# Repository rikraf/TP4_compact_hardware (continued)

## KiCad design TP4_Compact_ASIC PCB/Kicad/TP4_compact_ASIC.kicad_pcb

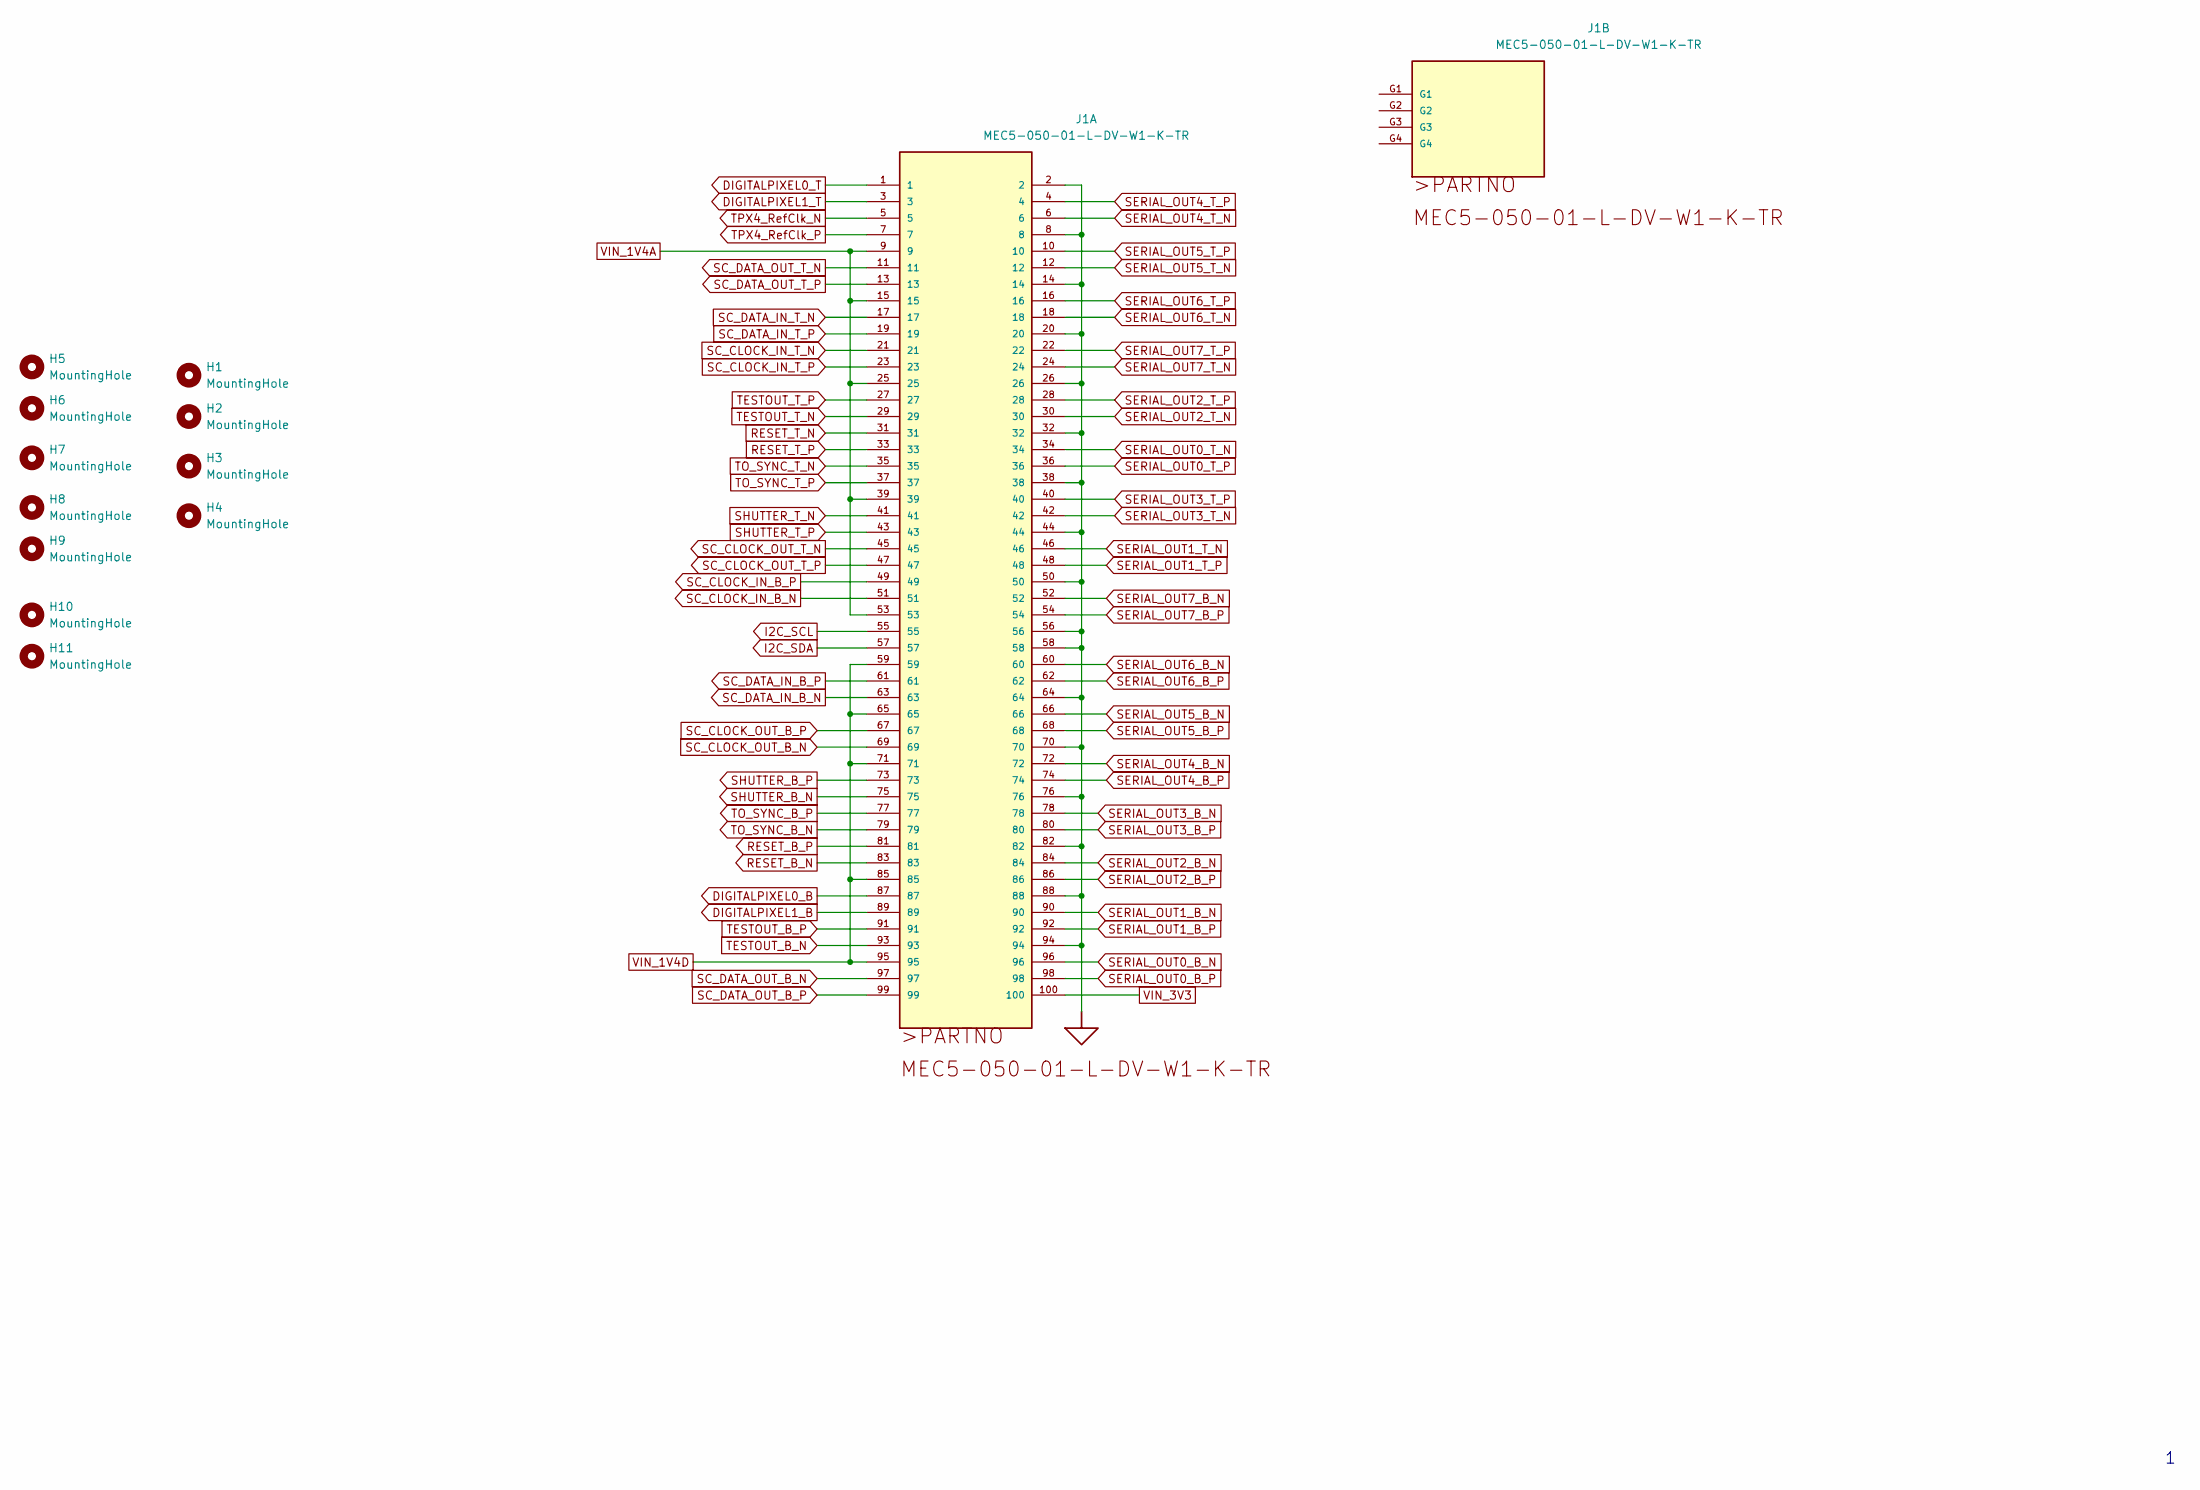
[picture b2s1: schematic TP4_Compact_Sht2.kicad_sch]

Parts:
H1, H2, H3, H4: MountingHole; hole_2.4mm
H5, H6, H7, H8, H9: MountingHole; pad_5.3_3.0mm
H10, H11: MountingHole; hole_1.7mm
J1: MEC5-050-01-L-DV-W1-K-TR; MANUFACTURER PART NUMBER MEC5-050-01-L-DV-W1-K-TR

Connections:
DIGITALPIXEL0_B: J1.87; also elsewhere on the board
DIGITALPIXEL0_T: J1.1; also elsewhere on the board
DIGITALPIXEL1_B: J1.89; also elsewhere on the board
DIGITALPIXEL1_T: J1.3; also elsewhere on the board
GND: J1.2, J1.8, J1.14, J1.20, J1.26, J1.32, J1.38, J1.44, J1.50, J1.56, J1.58, J1.64, J1.70, J1.76, J1.82, J1.88, J1.94; also elsewhere on the board
I2C_SCL: J1.55; also elsewhere on the board
I2C_SDA: J1.57; also elsewhere on the board
RESET_B_N: J1.83; also elsewhere on the board
RESET_B_P: J1.81; also elsewhere on the board
RESET_T_N: J1.31; also elsewhere on the board
RESET_T_P: J1.33; also elsewhere on the board
SC_CLOCK_IN_B_N: J1.51; also elsewhere on the board
SC_CLOCK_IN_B_P: J1.49; also elsewhere on the board
SC_CLOCK_IN_T_N: J1.21; also elsewhere on the board
SC_CLOCK_IN_T_P: J1.23; also elsewhere on the board
SC_CLOCK_OUT_B_N: J1.69; also elsewhere on the board
SC_CLOCK_OUT_B_P: J1.67; also elsewhere on the board
SC_CLOCK_OUT_T_N: J1.45; also elsewhere on the board
SC_CLOCK_OUT_T_P: J1.47; also elsewhere on the board
SC_DATA_IN_B_N: J1.63; also elsewhere on the board
SC_DATA_IN_B_P: J1.61; also elsewhere on the board
SC_DATA_IN_T_N: J1.17; also elsewhere on the board
SC_DATA_IN_T_P: J1.19; also elsewhere on the board
SC_DATA_OUT_B_N: J1.97; also elsewhere on the board
SC_DATA_OUT_B_P: J1.99; also elsewhere on the board
SC_DATA_OUT_T_N: J1.11; also elsewhere on the board
SC_DATA_OUT_T_P: J1.13; also elsewhere on the board
SERIAL_OUT0_B_N: J1.96; also elsewhere on the board
SERIAL_OUT0_B_P: J1.98; also elsewhere on the board
SERIAL_OUT0_T_N: J1.34; also elsewhere on the board
SERIAL_OUT0_T_P: J1.36; also elsewhere on the board
SERIAL_OUT1_B_N: J1.90; also elsewhere on the board
SERIAL_OUT1_B_P: J1.92; also elsewhere on the board
SERIAL_OUT1_T_N: J1.46; also elsewhere on the board
SERIAL_OUT1_T_P: J1.48; also elsewhere on the board
SERIAL_OUT2_B_N: J1.84; also elsewhere on the board
SERIAL_OUT2_B_P: J1.86; also elsewhere on the board
SERIAL_OUT2_T_N: J1.30; also elsewhere on the board
SERIAL_OUT2_T_P: J1.28; also elsewhere on the board
SERIAL_OUT3_B_N: J1.78; also elsewhere on the board
SERIAL_OUT3_B_P: J1.80; also elsewhere on the board
SERIAL_OUT3_T_N: J1.42; also elsewhere on the board
SERIAL_OUT3_T_P: J1.40; also elsewhere on the board
SERIAL_OUT4_B_N: J1.72; also elsewhere on the board
SERIAL_OUT4_B_P: J1.74; also elsewhere on the board
SERIAL_OUT4_T_N: J1.6; also elsewhere on the board
SERIAL_OUT4_T_P: J1.4; also elsewhere on the board
SERIAL_OUT5_B_N: J1.66; also elsewhere on the board
SERIAL_OUT5_B_P: J1.68; also elsewhere on the board
SERIAL_OUT5_T_N: J1.12; also elsewhere on the board
SERIAL_OUT5_T_P: J1.10; also elsewhere on the board
SERIAL_OUT6_B_N: J1.60; also elsewhere on the board
SERIAL_OUT6_B_P: J1.62; also elsewhere on the board
SERIAL_OUT6_T_N: J1.18; also elsewhere on the board
SERIAL_OUT6_T_P: J1.16; also elsewhere on the board
SERIAL_OUT7_B_N: J1.52; also elsewhere on the board
SERIAL_OUT7_B_P: J1.54; also elsewhere on the board
SERIAL_OUT7_T_N: J1.24; also elsewhere on the board
SERIAL_OUT7_T_P: J1.22; also elsewhere on the board
SHUTTER_B_N: J1.75; also elsewhere on the board
SHUTTER_B_P: J1.73; also elsewhere on the board
SHUTTER_T_N: J1.41; also elsewhere on the board
SHUTTER_T_P: J1.43; also elsewhere on the board
TESTOUT_B_N: J1.93; also elsewhere on the board
TESTOUT_B_P: J1.91; also elsewhere on the board
TESTOUT_T_N: J1.29; also elsewhere on the board
TESTOUT_T_P: J1.27; also elsewhere on the board
TO_SYNC_B_N: J1.79; also elsewhere on the board
TO_SYNC_B_P: J1.77; also elsewhere on the board
TO_SYNC_T_N: J1.35; also elsewhere on the board
TO_SYNC_T_P: J1.37; also elsewhere on the board
TPX4_RefClk_N: J1.5; also elsewhere on the board
TPX4_RefClk_P: J1.7; also elsewhere on the board
VIN_1V4A: J1.9, J1.15, J1.25, J1.39, J1.53; also elsewhere on the board
VIN_1V4D: J1.59, J1.65, J1.71, J1.85, J1.95; also elsewhere on the board
VIN_3V3: J1.100; also elsewhere on the board

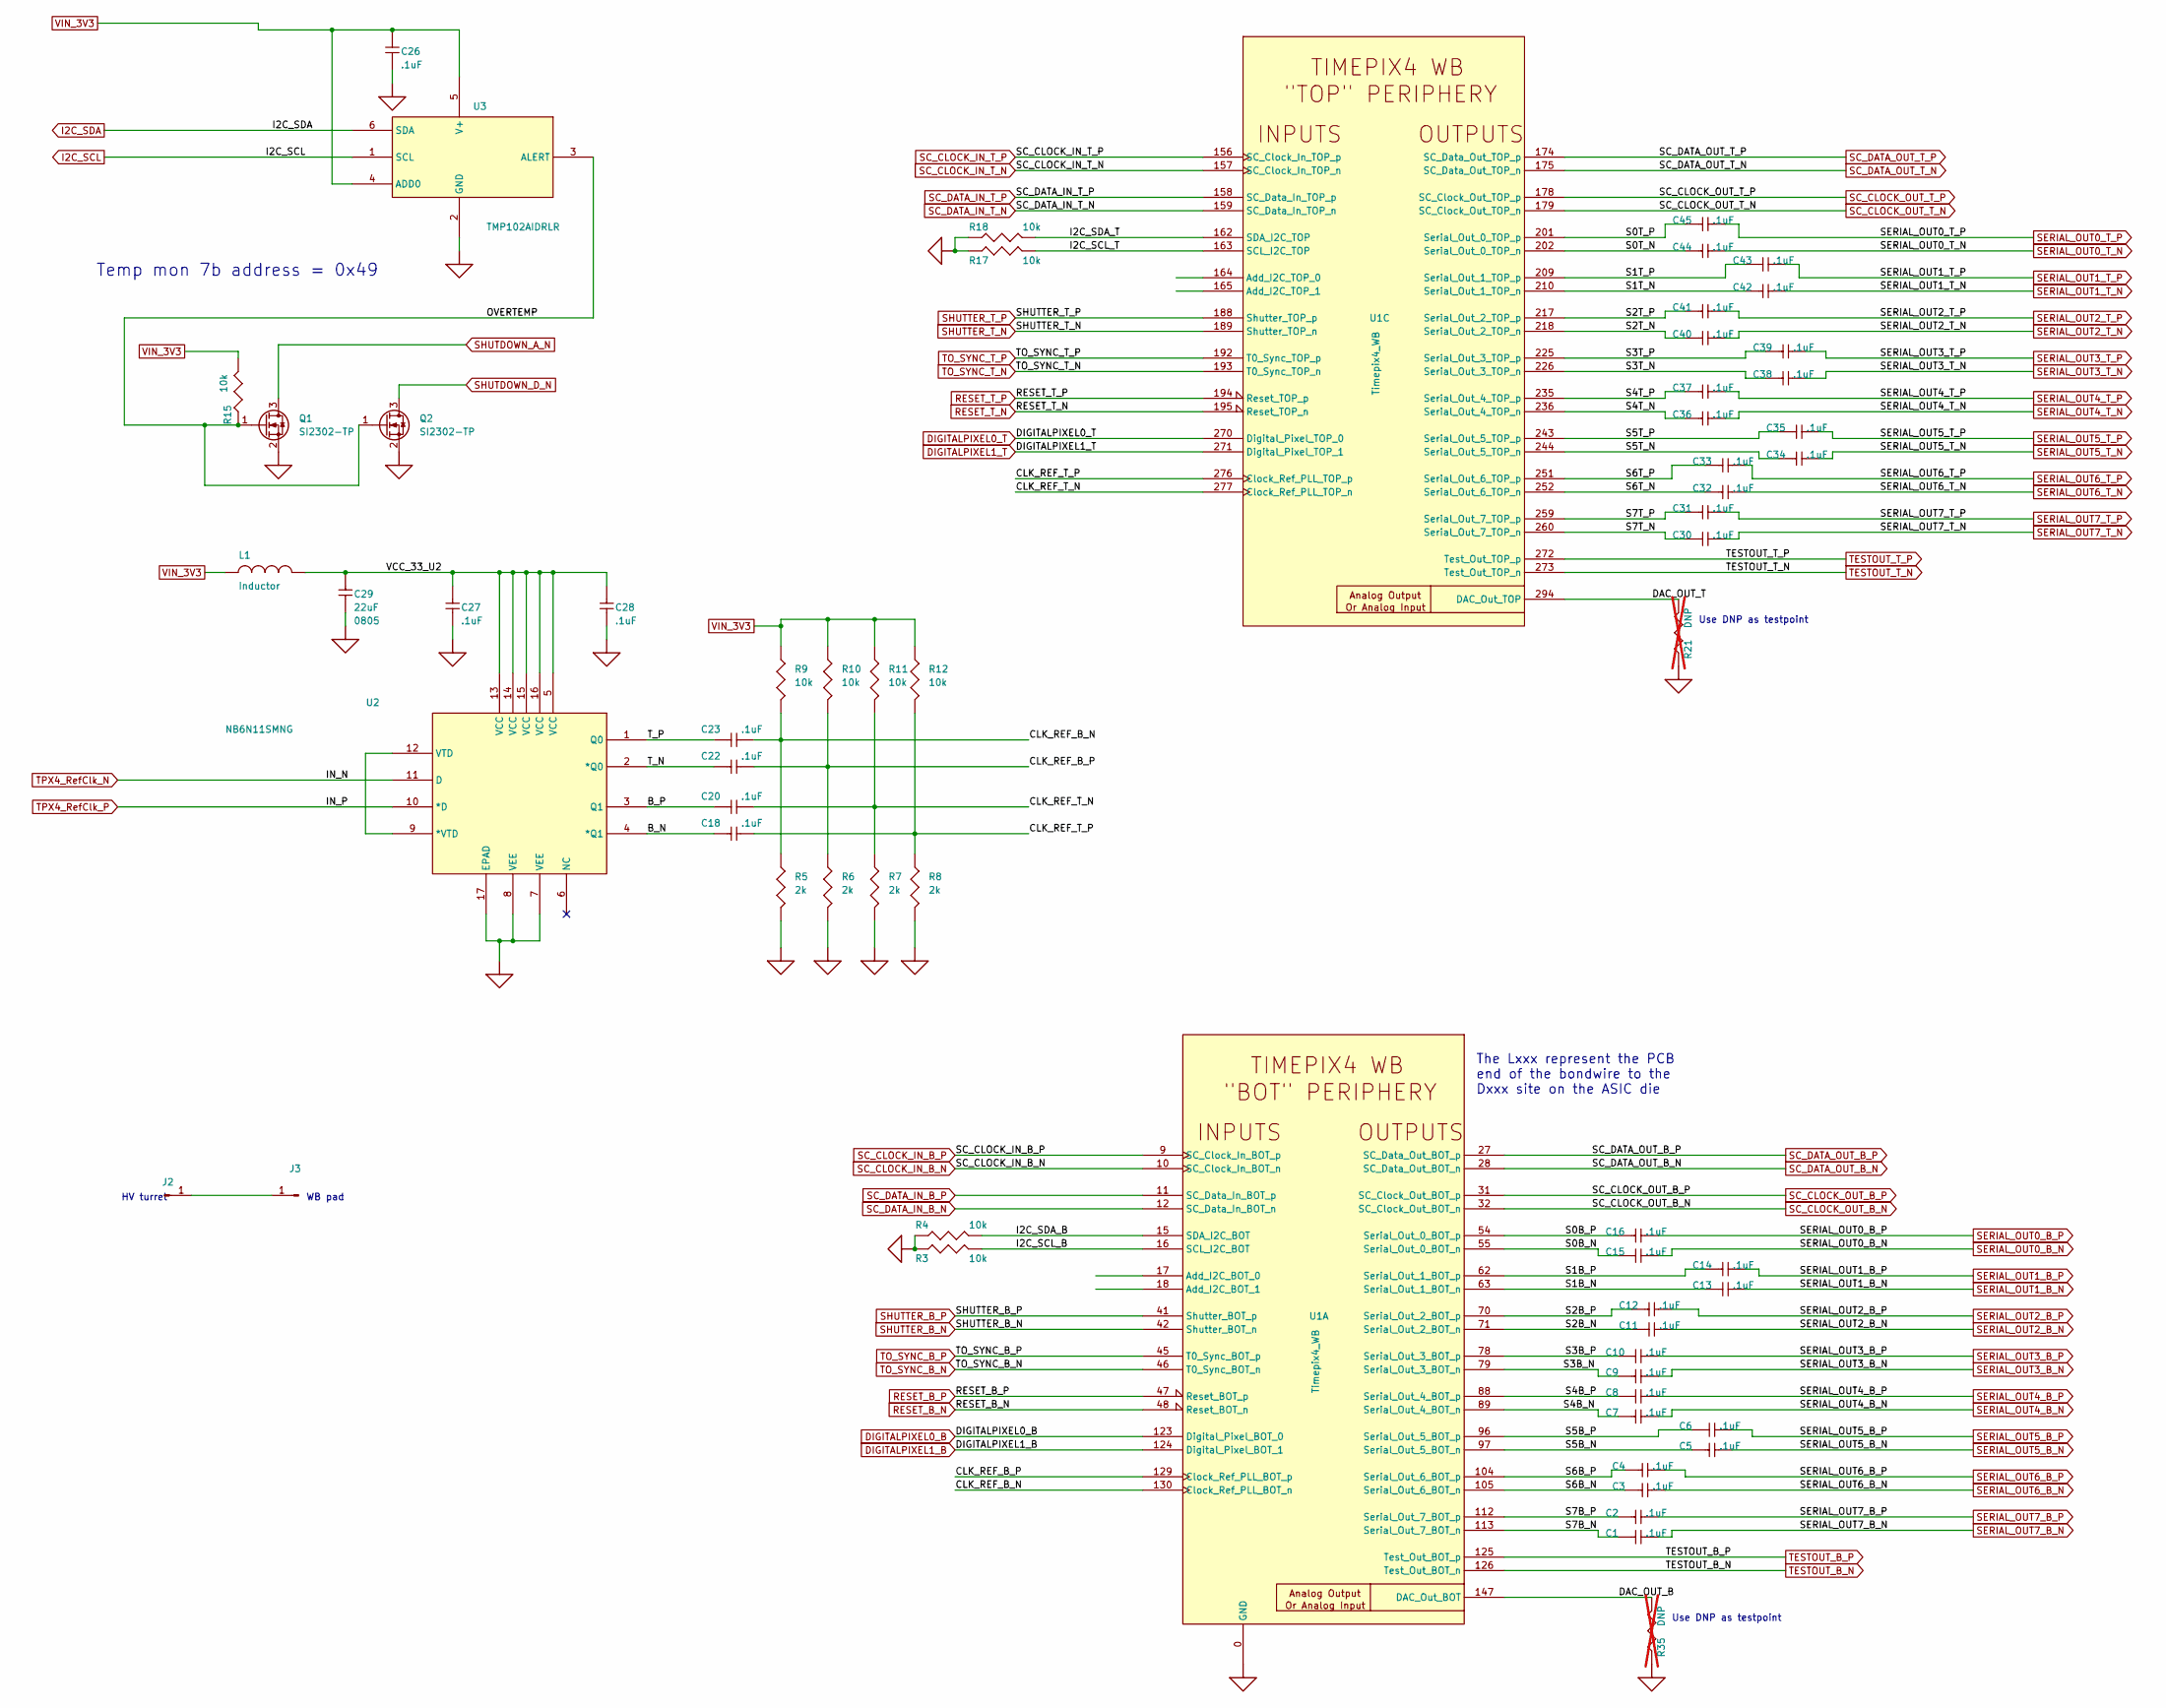
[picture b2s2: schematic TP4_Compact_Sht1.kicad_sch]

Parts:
C1, C2, C3, C4, C5, C6, C7, C8, C9, C10, C11, C12, C13, C14, C15, C16, C18, C20, C22, C23, C26, C27, C28, C30, C31, C32, C33, C34, C35, C36, C37, C38, C39, C40, C41, C42, C43, C44, C45: .1uF; C_0201_0603Metric; VOLTAGE - RATED 6.3V; TOLERANCE ±10%; MANUFACTURER PART NUMBER GRM033R61A104ME15D
C29: 22uF; C0805; VOLTAGE - RATED 10V; TOLERANCE ±10%; MANUFACTURER PART NUMBER CL21X226MQQNNNG
J2: Conn_01x01_Pin; PinHeader_1x01_P2.54mm_Vertical
J3: Conn_01x01_Pin; Single_WB_pad
L1: Inductor; L_0805_2012Metric; CURRENT RATING 4 Amps; MANUFACTURER PART NUMBER BLM21SP181BH1D
Q1, Q2: SI2302-TP; SOT-23; MANUFACTURER PART NUMBER SI2302-TP
R3, R4, R9, R10, R11, R12, R15, R17, R18: 10k; R_0402_1005Metric; MANUFACTURER PART NUMBER CR0402-FX-1002GLF
R5, R6, R7, R8: 2k; R_0402_1005Metric; MANUFACTURER PART NUMBER CR0402-FX-2001GLF
R21, R35: DNP; R_0402_1005Metric; not fitted
U1: Timepix4_WB; Timepix4_WB_nocaps
U2: NB6N11SMNG; QFN16_3x3_mm; MANUFACTURER_PART_NUMBER NB6L11SMNG
U3: TMP102AIDRLR; DRL6; MANUFACTURER_PART_NUMBER TMP102AIDRLR

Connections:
/ASIC_signals/B_N: C18.1, U2.4 (*Q1)
/ASIC_signals/B_P: C20.1, U2.3 (Q1)
/ASIC_signals/CLK_REF_B_N: C23.2, R5.2, R9.1, U1.130 (Clock_Ref_PLL_BOT_n)
/ASIC_signals/CLK_REF_B_P: C22.2, R6.2, R10.1, U1.129 (Clock_Ref_PLL_BOT_p)
/ASIC_signals/CLK_REF_T_N: C20.2, R7.2, R11.1, U1.277 (Clock_Ref_PLL_TOP_n)
/ASIC_signals/CLK_REF_T_P: C18.2, R8.2, R12.1, U1.276 (Clock_Ref_PLL_TOP_p)
/ASIC_signals/DAC_OUT_B: R35.2, U1.147 (DAC_Out_BOT)
/ASIC_signals/DAC_OUT_T: R21.2, U1.294 (DAC_Out_TOP)
/ASIC_signals/I2C_SCL_B: R3.2, U1.16 (SCL_I2C_BOT)
/ASIC_signals/I2C_SCL_T: R17.2, U1.163 (SCL_I2C_TOP)
/ASIC_signals/I2C_SDA_B: R4.2, U1.15 (SDA_I2C_BOT)
/ASIC_signals/I2C_SDA_T: R18.2, U1.162 (SDA_I2C_TOP)
/ASIC_signals/OVERTEMP: Q1.1 (G), Q2.1 (G), R15.1, U3.3 (ALERT)
/ASIC_signals/S0B_N: C15.1, U1.55 (Serial_Out_0_BOT_n)
/ASIC_signals/S0B_P: C16.1, U1.54 (Serial_Out_0_BOT_p)
/ASIC_signals/S0T_N: C44.1, U1.202 (Serial_Out_0_TOP_n)
/ASIC_signals/S0T_P: C45.1, U1.201 (Serial_Out_0_TOP_p)
/ASIC_signals/S1B_N: C13.1, U1.63 (Serial_Out_1_BOT_n)
/ASIC_signals/S1B_P: C14.1, U1.62 (Serial_Out_1_BOT_p)
/ASIC_signals/S1T_N: C42.1, U1.210 (Serial_Out_1_TOP_n)
/ASIC_signals/S1T_P: C43.1, U1.209 (Serial_Out_1_TOP_p)
/ASIC_signals/S2B_N: C11.1, U1.71 (Serial_Out_2_BOT_n)
/ASIC_signals/S2B_P: C12.1, U1.70 (Serial_Out_2_BOT_p)
/ASIC_signals/S2T_N: C40.1, U1.218 (Serial_Out_2_TOP_n)
/ASIC_signals/S2T_P: C41.1, U1.217 (Serial_Out_2_TOP_p)
/ASIC_signals/S3B_N: C9.1, U1.79 (Serial_Out_3_BOT_n)
/ASIC_signals/S3B_P: C10.1, U1.78 (Serial_Out_3_BOT_p)
/ASIC_signals/S3T_N: C38.1, U1.226 (Serial_Out_3_TOP_n)
/ASIC_signals/S3T_P: C39.1, U1.225 (Serial_Out_3_TOP_p)
/ASIC_signals/S4B_N: C7.1, U1.89 (Serial_Out_4_BOT_n)
/ASIC_signals/S4B_P: C8.1, U1.88 (Serial_Out_4_BOT_p)
/ASIC_signals/S4T_N: C36.1, U1.236 (Serial_Out_4_TOP_n)
/ASIC_signals/S4T_P: C37.1, U1.235 (Serial_Out_4_TOP_p)
/ASIC_signals/S5B_N: C5.1, U1.97 (Serial_Out_5_BOT_n)
/ASIC_signals/S5B_P: C6.1, U1.96 (Serial_Out_5_BOT_p)
/ASIC_signals/S5T_N: C34.1, U1.244 (Serial_Out_5_TOP_n)
/ASIC_signals/S5T_P: C35.1, U1.243 (Serial_Out_5_TOP_p)
/ASIC_signals/S6B_N: C3.1, U1.105 (Serial_Out_6_BOT_n)
/ASIC_signals/S6B_P: C4.1, U1.104 (Serial_Out_6_BOT_p)
/ASIC_signals/S6T_N: C32.1, U1.252 (Serial_Out_6_TOP_n)
/ASIC_signals/S6T_P: C33.1, U1.251 (Serial_Out_6_TOP_p)
/ASIC_signals/S7B_N: C1.1, U1.113 (Serial_Out_7_BOT_n)
/ASIC_signals/S7B_P: C2.1, U1.112 (Serial_Out_7_BOT_p)
/ASIC_signals/S7T_N: C30.1, U1.260 (Serial_Out_7_TOP_n)
/ASIC_signals/S7T_P: C31.1, U1.259 (Serial_Out_7_TOP_p)
/ASIC_signals/T_N: C22.1, U2.2 (*Q0)
/ASIC_signals/T_P: C23.1, U2.1 (Q0)
/ASIC_signals/VCC_33_U2: C27.1, C28.1, C29.1, L1.2, U2.5 (VCC), U2.13 (VCC), U2.14 (VCC), U2.15 (VCC), U2.16 (VCC)
DIGITALPIXEL0_B: U1.123 (Digital_Pixel_BOT_0); also elsewhere on the board
DIGITALPIXEL0_T: U1.270 (Digital_Pixel_TOP_0); also elsewhere on the board
DIGITALPIXEL1_B: U1.124 (Digital_Pixel_BOT_1); also elsewhere on the board
DIGITALPIXEL1_T: U1.271 (Digital_Pixel_TOP_1); also elsewhere on the board
GND: C26.2, C27.2, C28.2, C29.2, Q1.2 (S), Q2.2 (S), R3.1, R4.1, R5.1, R6.1, R7.1, R8.1, R17.1, R18.1, R21.1, R35.1, U1.0 (GND), U2.7 (VEE), U2.8 (VEE), U2.17 (EPAD), U3.2 (GND); also elsewhere on the board
I2C_SCL: U3.1 (SCL); also elsewhere on the board
I2C_SDA: U3.6 (SDA); also elsewhere on the board
unnamed: J2.1, J3.1
unnamed: U2.9 (*VTD), U2.12 (VTD)
RESET_B_N: U1.48 (Reset_BOT_n); also elsewhere on the board
RESET_B_P: U1.47 (Reset_BOT_p); also elsewhere on the board
RESET_T_N: U1.195 (Reset_TOP_n); also elsewhere on the board
RESET_T_P: U1.194 (Reset_TOP_p); also elsewhere on the board
SC_CLOCK_IN_B_N: U1.10 (SC_Clock_In_BOT_n); also elsewhere on the board
SC_CLOCK_IN_B_P: U1.9 (SC_Clock_In_BOT_p); also elsewhere on the board
SC_CLOCK_IN_T_N: U1.157 (SC_Clock_In_TOP_n); also elsewhere on the board
SC_CLOCK_IN_T_P: U1.156 (SC_Clock_In_TOP_p); also elsewhere on the board
SC_CLOCK_OUT_B_N: U1.32 (SC_Clock_Out_BOT_n); also elsewhere on the board
SC_CLOCK_OUT_B_P: U1.31 (SC_Clock_Out_BOT_p); also elsewhere on the board
SC_CLOCK_OUT_T_N: U1.179 (SC_Clock_Out_TOP_n); also elsewhere on the board
SC_CLOCK_OUT_T_P: U1.178 (SC_Clock_Out_TOP_p); also elsewhere on the board
SC_DATA_IN_B_N: U1.12 (SC_Data_In_BOT_n); also elsewhere on the board
SC_DATA_IN_B_P: U1.11 (SC_Data_In_BOT_p); also elsewhere on the board
SC_DATA_IN_T_N: U1.159 (SC_Data_In_TOP_n); also elsewhere on the board
SC_DATA_IN_T_P: U1.158 (SC_Data_In_TOP_p); also elsewhere on the board
SC_DATA_OUT_B_N: U1.28 (SC_Data_Out_BOT_n); also elsewhere on the board
SC_DATA_OUT_B_P: U1.27 (SC_Data_Out_BOT_p); also elsewhere on the board
SC_DATA_OUT_T_N: U1.175 (SC_Data_Out_TOP_n); also elsewhere on the board
SC_DATA_OUT_T_P: U1.174 (SC_Data_Out_TOP_p); also elsewhere on the board
SERIAL_OUT0_B_N: C15.2; also elsewhere on the board
SERIAL_OUT0_B_P: C16.2; also elsewhere on the board
SERIAL_OUT0_T_N: C44.2; also elsewhere on the board
SERIAL_OUT0_T_P: C45.2; also elsewhere on the board
SERIAL_OUT1_B_N: C13.2; also elsewhere on the board
SERIAL_OUT1_B_P: C14.2; also elsewhere on the board
SERIAL_OUT1_T_N: C42.2; also elsewhere on the board
SERIAL_OUT1_T_P: C43.2; also elsewhere on the board
SERIAL_OUT2_B_N: C11.2; also elsewhere on the board
SERIAL_OUT2_B_P: C12.2; also elsewhere on the board
SERIAL_OUT2_T_N: C40.2; also elsewhere on the board
SERIAL_OUT2_T_P: C41.2; also elsewhere on the board
SERIAL_OUT3_B_N: C9.2; also elsewhere on the board
SERIAL_OUT3_B_P: C10.2; also elsewhere on the board
SERIAL_OUT3_T_N: C38.2; also elsewhere on the board
SERIAL_OUT3_T_P: C39.2; also elsewhere on the board
SERIAL_OUT4_B_N: C7.2; also elsewhere on the board
SERIAL_OUT4_B_P: C8.2; also elsewhere on the board
SERIAL_OUT4_T_N: C36.2; also elsewhere on the board
SERIAL_OUT4_T_P: C37.2; also elsewhere on the board
SERIAL_OUT5_B_N: C5.2; also elsewhere on the board
SERIAL_OUT5_B_P: C6.2; also elsewhere on the board
SERIAL_OUT5_T_N: C34.2; also elsewhere on the board
SERIAL_OUT5_T_P: C35.2; also elsewhere on the board
SERIAL_OUT6_B_N: C3.2; also elsewhere on the board
SERIAL_OUT6_B_P: C4.2; also elsewhere on the board
SERIAL_OUT6_T_N: C32.2; also elsewhere on the board
SERIAL_OUT6_T_P: C33.2; also elsewhere on the board
SERIAL_OUT7_B_N: C1.2; also elsewhere on the board
SERIAL_OUT7_B_P: C2.2; also elsewhere on the board
SERIAL_OUT7_T_N: C30.2; also elsewhere on the board
SERIAL_OUT7_T_P: C31.2; also elsewhere on the board
SHUTDOWN_A_N: Q1.3 (D); also elsewhere on the board
SHUTDOWN_D_N: Q2.3 (D); also elsewhere on the board
SHUTTER_B_N: U1.42 (Shutter_BOT_n); also elsewhere on the board
SHUTTER_B_P: U1.41 (Shutter_BOT_p); also elsewhere on the board
SHUTTER_T_N: U1.189 (Shutter_TOP_n); also elsewhere on the board
SHUTTER_T_P: U1.188 (Shutter_TOP_p); also elsewhere on the board
TESTOUT_B_N: U1.126 (Test_Out_BOT_n); also elsewhere on the board
TESTOUT_B_P: U1.125 (Test_Out_BOT_p); also elsewhere on the board
TESTOUT_T_N: U1.273 (Test_Out_TOP_n); also elsewhere on the board
TESTOUT_T_P: U1.272 (Test_Out_TOP_p); also elsewhere on the board
TO_SYNC_B_N: U1.46 (T0_Sync_BOT_n); also elsewhere on the board
TO_SYNC_B_P: U1.45 (T0_Sync_BOT_p); also elsewhere on the board
TO_SYNC_T_N: U1.193 (T0_Sync_TOP_n); also elsewhere on the board
TO_SYNC_T_P: U1.192 (T0_Sync_TOP_p); also elsewhere on the board
TPX4_RefClk_N: U2.11 (D); also elsewhere on the board
TPX4_RefClk_P: U2.10 (*D); also elsewhere on the board
VIN_3V3: C26.1, L1.1, R9.2, R10.2, R11.2, R12.2, R15.2, U3.4 (ADD0), U3.5 (V+); also elsewhere on the board

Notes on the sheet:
HV turret
Use DNP as testpoint
WB pad
Temp mon 7b address = 0x49
The Lxxx represent the PCB end of the bondwire to the Dxxx site on the ASIC die
